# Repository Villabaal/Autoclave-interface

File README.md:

# Autoclave Interface
## Platformio project with avr-gcc 11.2
Autoclave interface (atmega328P) programmed on platformIO with the arduino framework using c++20 connected via R232 to its Controller.

## Kicad project
Folder with kicad files, Schematic, PCB, components list.

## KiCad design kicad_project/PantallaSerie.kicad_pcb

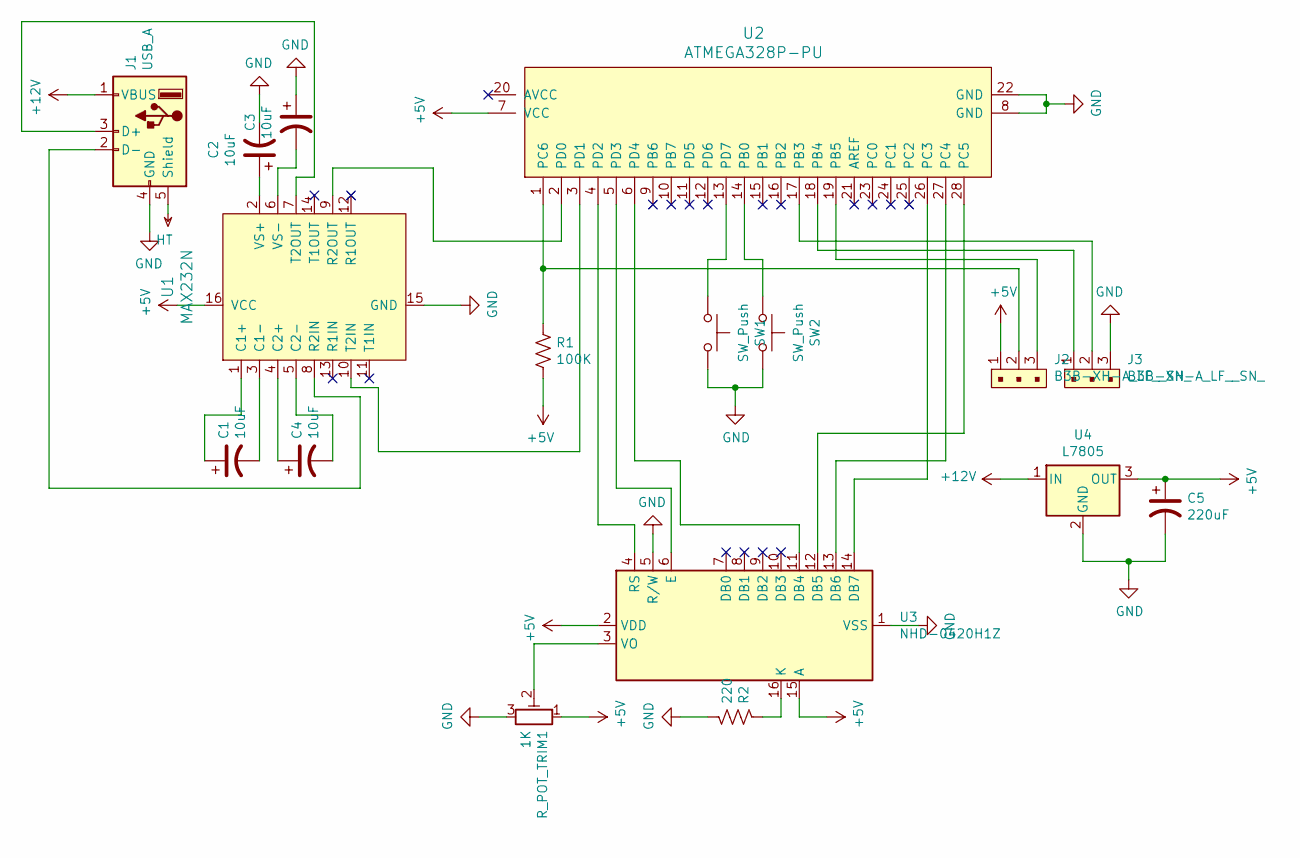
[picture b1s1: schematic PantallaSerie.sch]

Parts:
C1, C2, C3, C4: 10uF; CP_Radial_D4.0mm_P2.00mm
C5: 220uF; CP_Radial_D5.0mm_P2.50mm
J1: USB_A; USB_A_CONNFLY_DS1095-WNR0
J2, J3: B3B-XH-A_LF__SN_; PinHeader_1x03_P2.54mm_Vertical; MPN B3B-XH-A(LF)(SN); Digi-Key_PN 455-2248-ND
R1: 100K; R_Axial_DIN0411_L9.9mm_D3.6mm_P12.70mm_Horizontal
R2: 220; R_Axial_DIN0411_L9.9mm_D3.6mm_P12.70mm_Horizontal
R_POT_TRIM1: 1K; Potentiometer_Bourns_3299W_Vertical
SW1, SW2: SW_Push; push_button_Raga
U1: MAX232N; DIP-16_W7.62mm; MPN MAX232N; Digi-Key_PN 296-1402-5-ND
U2: ATMEGA328P-PU; DIP-28_W7.62mm; MPN ATMEGA328P-PU; Digi-Key_PN ATMEGA328P-PU-ND
U3: NHD-0420H1Z; WC1602A
U4: L7805; TO-220F-3_Horizontal_TabDown

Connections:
+5V: C5.1, J2.1, R1.2, R_POT_TRIM1.1, U1.16 (VCC), U2.7 (VCC), U3.2 (VDD), U3.15 (A), U4.3 (OUT)
+12V: J1.1 (VBUS), U4.1 (IN)
GND: C2.2, C3.1, C5.2, J1.4 (GND), J3.3, R2.2, R_POT_TRIM1.3, SW1.2, SW2.2, U1.15 (GND), U2.8 (GND), U2.22 (GND), U3.1 (VSS), U3.5 (R/W), U4.2 (GND)
HT: J1.5 (Shield)
unnamed: C1.1, U1.1 (C1+)
unnamed: C1.2, U1.3 (C1-)
unnamed: C2.1, U1.2 (VS+)
unnamed: C3.2, U1.6 (VS-)
unnamed: C4.1, U1.4 (C2+)
unnamed: C4.2, U1.5 (C2-)
unnamed: J1.2 (D-), U1.8 (R2IN)
unnamed: J1.3 (D+), U1.7 (T2OUT)
unnamed: J2.2, R1.1, U2.1 (PC6)
unnamed: J2.3, U2.19 (PB5)
unnamed: J3.1, U2.18 (PB4)
unnamed: J3.2, U2.17 (PB3)
unnamed: R2.1, U3.16 (K)
unnamed: R_POT_TRIM1.2, U3.3 (VO)
unnamed: SW1.1, U2.13 (PD7)
unnamed: SW2.1, U2.14 (PB0)
unnamed: U1.9 (R2OUT), U2.2 (PD0)
unnamed: U1.10 (T2IN), U2.3 (PD1)
unnamed: U2.4 (PD2), U3.4 (RS)
unnamed: U2.5 (PD3), U3.6 (E)
unnamed: U2.6 (PD4), U3.11 (DB4)
unnamed: U2.26 (PC3), U3.14 (DB7)
unnamed: U2.27 (PC4), U3.13 (DB6)
unnamed: U2.28 (PC5), U3.12 (DB5)

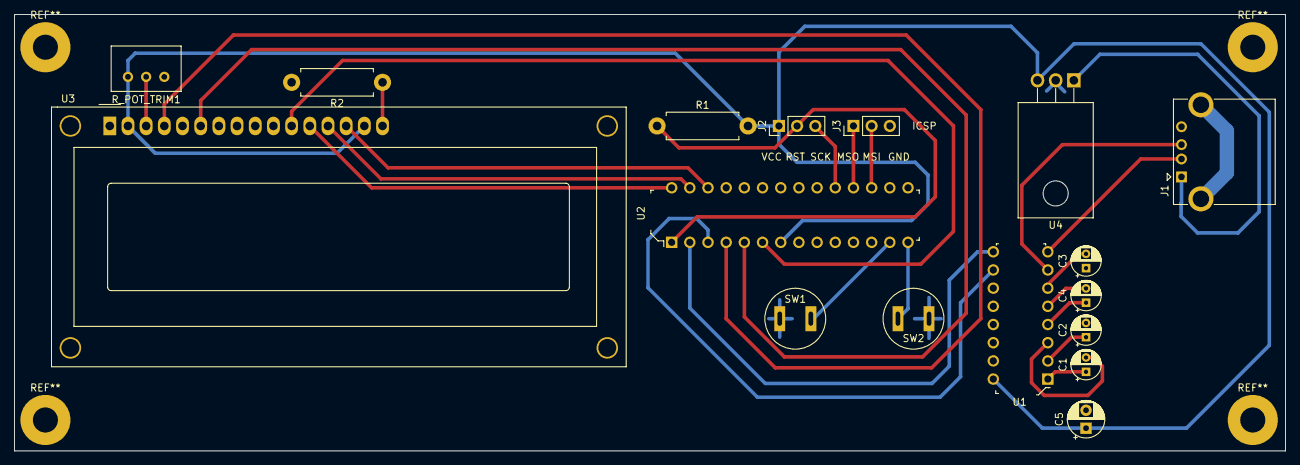
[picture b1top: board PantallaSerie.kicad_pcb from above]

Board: 2 copper layers, 177.5 x 61.0 mm, 17 parts (0 on the bottom side), 27 nets.

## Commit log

2023-07-10 autoclave interface screen
